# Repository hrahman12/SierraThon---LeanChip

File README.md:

<p align="center"><b>Does the 2D design really become the 3D board? LeanChip proves it with the Lean 4 kernel,</b><br>
for the Sierrathon RP2040 board and its exact 21-line parts list.</p>

# LeanChip: 2D → 3D, verified in Lean

*Built for Sierrathon 2026: design a manufacturable, cost-effective board from the provided RP2040 schematic and BOM.*

## The question

A PCB starts as flat documents: a schematic, a parts list, a stack-up drawing, footprints. It ends as a physical object. **Does the first really turn into the second?**

| 2D design | Lean ⊢ | 3D board |
|---|---|---|
| Schematic pins and nets, BOM part numbers, footprints and courtyards, the 4-layer stack-up | Right part on every footprint, every pin on the right net, every 3D body inside its courtyard, no two parts able to collide, everything on the board | A KiCad STEP assembly with real part models: 49 bodies on a 52 × 45 mm hexagon, 59.5 mil thick |

You feed the tool a board file. It answers 🟢 **green** (proved), 🟡 **yellow** (buildable, needs an action) or 🔴 **red** (not the design you meant). The answer only counts when the Lean kernel has certified it.

## See it run

```
$ python3 leanvsdfm/tools/leancheck.py leanvsdfm/pcb/sierrathon.kicad_pcb

  Board
     GREEN    Every schematic part is placed and on the BOM
     GREEN    Footprint package matches the BOM part number
     YELLOW   Manufacturer footprint used (not a library stand-in)      J1, SW1, SW2, SW3
     GREEN    Every schematic pin is on the right net (schematic ↔ PCB)
     GREEN    No connections that are not on the schematic
     GREEN    LED polarity (cathode to GND)
     GREEN    U3 land pattern = manufacturer (UltraLibrarian)
     GREEN    Preferred land pattern (IPC nominal / manufacturer), not a variant
  3D fit
     GREEN    Every 3D body sits inside its own courtyard
     GREEN    No two courtyards overlap, so no two bodies can collide
     GREEN    Pads and bodies are on the board (inside the outline)
     GREEN    Every drilled hole is at least 8 mil
     YELLOW   Every part has a 3D body model                            J1
  Package
     YELLOW   BOM quantities match the designator lists                 row 5: qty 8 but 7 designators
     YELLOW   Inner copper: stack-up agrees with instructions           0.5 oz vs 1 oz
     GREEN    Stack-up thickness within 62 mil ± 10 %                   59.5 mil
     GREEN    90 Ω pairs use the stack-up geometry (5/4 mil), all other nets ≥ 6 mil
  Specs
     YELLOW   LED current within the RP2040 default 4 mA drive          needs the 8 mA setting
     GREEN    AP2112 junction temperature < 125 °C                      106 °C worst case
     GREEN    USB clock exactly 48 MHz
     GREEN    QSPI clock within W25Q128 limit

  OVERALL  YELLOW    certified by the Lean kernel (decide +kernel)
  3D envelope: board 1.5112 mm + tallest body 4.3 mm = 5.811 mm   | theorem: no two bodies overlap
```

Detail text is shortened here. The same run as an HTML report: [`leanvsdfm/reports/sierrathon.html`](leanvsdfm/reports/sierrathon.html) ([picture](leanvsdfm/reports/sierrathon.png)).

## The 3D board

This is a render of [`leanvsdfm/out3d/sierrathon.step`](leanvsdfm/out3d), the STEP file **KiCad exported from our placed board**, with KiCad's own 3D part models and the manufacturer's model for the flash chip. Nothing in it is drawn by hand.

- **54 parts** placed in a 52 × 45 mm hexagon, zero courtyard overlaps, the four M4 holes included.
- **49 measured bodies.** OpenCascade measures each 3D model; Lean places it from the footprint's position and rotation.
- **Lean and KiCad agree.** KiCad's STEP exporter places the same models on its own. The two agree on all 49 body outlines to under 0.05 µm; heights differ by a fixed 50 µm. That comparison is a test (`tools/check_step_agreement.py`), not a proof.
- **The real stack-up is in the KiCad file:** 59.496 mil, layer by layer, from the Sierrathon drawing.

## How it works

```mermaid
flowchart LR
    A["2D design<br/>schematic · BOM · stack-up · footprints"] --> B["KiCad API reads the board<br/>exact nanometres"]
    M["3D part models<br/>STEP files"] --> C["OpenCascade measures<br/>each body"]
    B --> L{"Lean checks<br/>parts · pins · 3D fit · specs"}
    C --> L
    L -->|"all proved"| G["🟢 GREEN"]
    L -->|"needs an action"| Y["🟡 YELLOW"]
    L -->|"not the intended design"| R["🔴 RED"]
    L --> K["Kernel certifies the findings<br/>as a theorem"]
    R --> F["Fixer searches real options<br/>and proves the fix"]
    F --> B
    style L fill:#1A1F2B,stroke:#B9A7FF,color:#F3EFE6
    style K fill:#1A1F2B,stroke:#B9A7FF,color:#F3EFE6
```

The heart of the 3D check is one theorem, proved once for every possible board ([`Fit3D.lean`](leanvsdfm/LeanVsDFM/Fit3D.lean)):

```lean
/-- If the checker accepts a board, no two part bodies overlap. -/
theorem bodies_never_collide (ps : List Part) (h : fitOk ps = true) : ps.Pairwise bodySep
```

and then applied to our board, where the kernel checks the hypothesis ([`Verify.lean`](leanvsdfm/LeanVsDFM/Verify.lean)):

```lean
theorem our_board_fits : Fit3D.fit3d PcbData.outline PcbData.parts = [] := by decide +kernel

theorem our_board_bodies_never_collide : PcbData.parts.Pairwise Fit3D.bodySep :=
  Fit3D.bodies_never_collide _ (by decide +kernel)
```

`leancheck` does the same for any board you give it: it writes `theorem certified : verify board = [the findings]` and asks the kernel. If the kernel says no, the report says **not certified**.

### Lean and DFM look at different things

| | A DFM check | Lean, here |
|---|---|---|
| Looks at | Fabrication geometry: trace width and spacing, drills, annular rings, solder mask | Intent: the schematic, the BOM, the part numbers, the measured bodies |
| A footprint for the wrong part, with clean geometry | passes | 🔴 wrong package |
| A reversed LED | passes | 🔴 polarity and wrong net |
| The mandated 5/4 mil USB pairs under one global 6 mil rule | flags them | 🟢 knows which nets are impedance nets |
| Result | a list of warnings | a theorem the kernel has checked |

We did not run a commercial DFM tool on this board (it is not routed yet); this table compares what each kind of check examines.

## Demo boards

Five real KiCad files in [`leanvsdfm/pcb/`](leanvsdfm/pcb): our board, and the same board with one realistic mistake each. Every verdict is certified.

| Board | Verdict | What Lean reports |
|---|---|---|
| `sierrathon.kicad_pcb` (ours) | 🟡 YELLOW | Board and 3D fit proved; 4 parts on library stand-ins, J1 has no 3D model, plus the package issues below |
| `fault_led_reversed` | 🔴 RED | D5 pad 1 on `LED3_A`, schematic says `GND`; cathode not on GND |
| `fault_narrow_flash` | 🔴 RED | U3 is `SOIC-8_3.9x4.9mm`; the W25Q128JVSIQ needs `SOIC-8_5.23x5.23mm` |
| `fault_wrong_cap_size` | 🔴 RED | C4 is 0603 on an 0402 line **and** its courtyard now overlaps its neighbours |
| `fault_flash_pins_swapped` | 🔴 RED | U3 pad 2 on `QSPI_D0`, schematic says `QSPI_D1` (and pad 5 the reverse) |

## AI proposes, Lean decides

Anything may propose a way to build the board: a script, or an AI. Proposers are untrusted. Each proposal becomes a real board file with the footprints swapped in place, and Lean rates it. **51 builds, all certified: 16 yellow, 35 red.**

These six were written by Claude, with a reason for each, before Lean rated them ([`explore/ai_proposals.json`](leanvsdfm/explore/ai_proposals.json)):

| AI proposal | Its reasoning | Lean | Why |
|---|---|---|---|
| Keep it nominal | IPC-nominal land patterns everywhere and the manufacturer pattern for the flash: the safest choice for reflow assembly. | 🟡 YELLOW | same as our build |
| Thermal vias under the rp2040 | Use KiCad's thermal-via QFN footprint so the exposed pad can dump heat into the inner planes. | 🔴 RED | the footprint's 0.2 mm vias are below the 8 mil minimum drill |
| Hand-solder the big passives | The 0603 and 0805 parts are the ones a person would rework by hand, so give only those the longer hand-solder pads. | 🟡 YELLOW | fits; reported as variant land patterns |
| Wider soic for the flash | KiCad's 5.275 mm SOIC-8 footprint also targets 208 mil bodies and has slightly longer pads. | 🟡 YELLOW | fits; reported as a variant land pattern |
| Hand-solder the crystal | The 3225 crystal has pads under the body; the hand-solder footprint exposes them for an iron. | 🔴 RED | its larger courtyard overlaps R7, R13, R14 and R17 |
| Hand-solder leds and regulator | LEDs are polarised and often replaced, and the regulator is the hottest part; longer pads make both easier to rework. | 🟡 YELLOW | fits; reported as variant land patterns |

Two plausible ideas were wrong, and Lean said exactly why.

Changing **one** BOM line to its hand-solder variant stays yellow for most lines, but turns red for the 27 Ω USB resistors, the ESD chip and the crystal, because their larger courtyards collide on this compact board.

## Where the supplied package breaks

Four problems in the official Sierrathon files, marked on the files themselves. Each is a Lean theorem in [`Breaks.lean`](leanvsdfm/LeanVsDFM/Breaks.lean).

| # | Break | Lean catches it | Fix |
|---|---|---|---|
| 1 | BOM row 5 says **Qty 8**, lists **7** designators; the schematic draws 7 LEDs | `break1_only_row5`, `break1_schematic_has_7_leds` | set quantity to the designator count; only row 5 changes (`break1_fix_changes_only_row5`) |
| 2 | Stack-up draws **0.5 oz** inner copper; instructions say **1 oz** | `break2_conflict` | ask the fab; both readings meet 62 mil ± 10 % (`break2_both_readings_buildable`) |
| 3 | 330 Ω LEDs draw up to **4.945 mA**, above the RP2040's 4 mA default pin drive | `break3_default_drive_fails` | set GPIO17–23 to 8 mA (`break3_fixed_by_8mA`); BOM unchanged |
| 4 | The mandated **5/4 mil** 90 Ω pairs fail a global **6 mil** rule | `break4_dfm_flags_mandated_geometry` | rule per net class (`break4_lean_accepts_pairs`, `break4_lean_still_enforces_6mil`) |

## The proofs, as formulas

Each formula is a theorem the Lean kernel has checked.

**No two bodies overlap** (`Fit3D.bodies_never_collide`, with `Fit3D.sep_of_inside`):

$$\text{fitOk}(ps)\ \Longrightarrow\ \forall\, p \neq q:\ \text{body}(p)\cap\text{body}(q)=\varnothing \qquad\qquad a\subseteq A,\ b\subseteq B,\ A\cap B=\varnothing\ \Longrightarrow\ a\cap b=\varnothing$$

**Where a 3D body lands on the board** (`Fit3D.bodyBox`), with θ a right angle:

$$\binom{x}{y}_{\text{board}}=\binom{p_x}{p_y}+R_\theta\binom{m_x}{-m_y}$$

**Inside the convex board outline** (`Fit3D.pointIn`): the cross product has one sign for every edge (a, b):

$$(b-a)\times(c-a)\ \ge 0$$

**Stack-up thickness** (`Specs.stackup_within_tolerance`):

$$0.5+1.5+4.348+0.6+45.6+0.6+4.348+1.5+0.5 = 59.496\ \text{mil} \in 62 \pm 10\%$$

**LED current** (`Breaks.break3_default_drive_fails`, `Fixers.led_design`):

$$I_{\max}=\frac{V_{DD,\max}-V_{f,\min}}{0.95\,R}=\frac{3.35-1.8}{313.5\ \Omega}=4.945\ \text{mA} > 4\ \text{mA}, \qquad 7\,I_{\max} = 34.6\ \text{mA} \le 50\ \text{mA}$$

**Regulator junction temperature** (`Specs.ldo_junction_ok`):

$$T_j = T_a + \theta_{JA}\,(V_{BUS,\max}-V_{out,\min})\,I = 50 + 250\cdot 2.0\cdot 0.112 = 106^\circ\text{C} < 125^\circ\text{C}$$

**Crystal load** (`Specs.crystal_load_window`), for every stray capacitance from 2 to 5 pF:

$$C_L=\frac{C_6C_7}{C_6+C_7}+C_s = 7.5 + C_s \in [9.5,\ 12.5]\ \text{pF}$$

**ADC supply filter** (`Specs.adc_filter_corner`), for every in-tolerance R and C and every π between 3.141 and 3.142:

$$313 \le \frac{1}{2\pi RC} \le 424\ \text{Hz}$$

**Differential impedance in tolerance** (`Breaks.break4_impedance_in_tolerance`), **BOM self-consistency** (`Breaks.break1_only_row5`), **fixers are correct** (`Fixers.find?_sound`), **overall colour is the worst row** (`Report.overall_is_worst`):

$$0.9\cdot 90 \le 89.7 \le 1.1\cdot 90\ \Omega \qquad \lbrace r : \text{qty}(r)\ne \text{count}(r)\rbrace=\lbrace 5\rbrace \qquad \text{find?}\ p\ l=\text{some}\ a \Rightarrow p(a)\wedge a\in l \qquad \forall r:\ \text{rank}(r)\le\text{rank}(\text{overall})$$

The [theorem table](docs/THEOREMS.md) covers 98 theorems across seven modules, including the web checker. The proofs use Lean's three standard axioms.

## Figures

| | |
|---|---|
|  |  |
|  |  |
|  |  |
|  |  |

Every figure is drawn from real data: the certified runs, the KiCad board, or the exact functions proved in Lean (`leanvsdfm/tools/viz.py`).

## With Claude Code

The repository ships slash commands and a skill ([`.claude/`](.claude)), so you can ask in plain words.

| Command | What it does |
|---|---|
| `/leancheck [board]` | Verdict for a board, row by row |
| `/explore [n]` | Propose n builds and let Lean rate them |
| `/verify` | Rebuild every proof and audit the axioms |
| `/board3d` | Export STEP and test it against Lean's placement |

A real exchange from building this project:

```
You:    Does Lean's idea of where the parts are in 3D match KiCad's STEP export?
Claude: $ python3 tools/check_step_agreement.py out3d/sierrathon_parts.json
        49 Lean bodies vs 49 bodies in KiCad's STEP export: largest outline (x, y)
        difference 0.0 µm, largest height difference 50 µm -> PASS
```

## Run it locally

You need Lean 4 (through elan) and KiCad 7 with its Python module. On Windows, use WSL with Ubuntu 24.04.

```bash
sudo apt install kicad kicad-footprints
```

```bash
curl -sSf https://raw.githubusercontent.com/leanprover/elan/master/elan-init.sh | sh
```

```bash
cd leanvsdfm && lake build
```

```bash
python3 tools/leancheck.py pcb/sierrathon.kicad_pcb --html report.html
```

`lake build` checks every proof. In text and JSON modes, `leancheck` exits 0 for certified green or yellow, 3 for red, and 4 if certification fails. The web API returns a red report with HTTP 422. Yellow findings are accepted design warnings and still require review.

From the repository root, run the fabrication gate separately with KiCad 9.

```bash
python3 leanvsdfm/tools/check_drc.py leanvsdfm/pcb/sierrathon.kicad_pcb --report /tmp/sierrathon-drc.json
```

This command exits 3 for DRC errors or unconnected items, 0 when only warnings or no findings remain, and 2 if DRC cannot run.

Check the exported component solids with OpenCascade using the `OCP` Python module.

```bash
python3 leanvsdfm/tools/check_step_collisions.py leanvsdfm/out3d/sierrathon.step --expected-components 49
```

The check uses OpenCascade solid intersections for candidate pairs. Shared volume above `1e-9 mm³` blocks the check. The expected count covers the modeled components in the current export and excludes the PCB substrate.

For live proposals on Vercel, set `ANTHROPIC_API_KEY` as a sensitive server-side variable for the project's Production environment, then redeploy. If the Anthropic project requires a different model, set `LEANCHIP_MODEL` to a model ID available to that project.

## Repository

```
├── leanvsdfm/               the project
│   ├── LeanVsDFM/           Lean: PartsVerifier · Fit3D · Breaks · Fixers · Specs · Report · Verify
│   ├── tools/               leancheck, board builder and placer, STEP tools, explorer, figures
│   ├── pcb/                 our board and four fault boards (KiCad 7)
│   ├── out3d/               the STEP and GLB that KiCad and OpenCascade produced
│   ├── models3d/            the 3D part models used, with their measured sizes
│   ├── explore/             51 rated builds, including the AI proposals
│   └── reports/             HTML reports
├── netlist/                 the schematic as a netlist (transcribed from the PDF)
├── altium/                  Altium symbol and footprint libraries
├── site/                    the website
├── assets/                  banner, figures, the marked-up Sierrathon files
├── .claude/                 Claude Code commands and skill
└── archive/                 earlier directions, kept for history
```

## What this does not do yet

- **Fabrication is blocked.** KiCad 9.0.2 DRC reports 124 unconnected items and 79 silkscreen warnings on the supplied board. Routing and a fabrication-ready DFM review remain open.
- **Four parts use library stand-ins** (USB-C J1, switches SW1 to SW3). Their manufacturer footprints and 3D models are needed; the report keeps them yellow until then.
- **3D fit has two checks.** Lean proves separation for the measured bounding boxes. OpenCascade checks shared solid volume directly in the STEP export. The current export covers 49 component bodies and is missing J1.
- **Schematic provenance.** `python3 netlist/build_netlist.py --check` verifies the supplied PDF and BOM hashes and reproduces the 39-net transcription. Comparing connectivity directly with the schematic requires the native EDA design or its exported netlist.
- **Electrical inputs.** Raspberry Pi's SDK confirms the 4 mA reset setting and the nominal 2, 4, 8 and 12 mA pad-drive options. The thermal resistance, ambient temperature, load budget, LED forward voltage and stray capacitance still need design-specific validation. [RP2040 pad registers](https://github.com/raspberrypi/pico-sdk/blob/2.2.0/src/rp2040/hardware_regs/include/hardware/regs/pads_bank0.h)

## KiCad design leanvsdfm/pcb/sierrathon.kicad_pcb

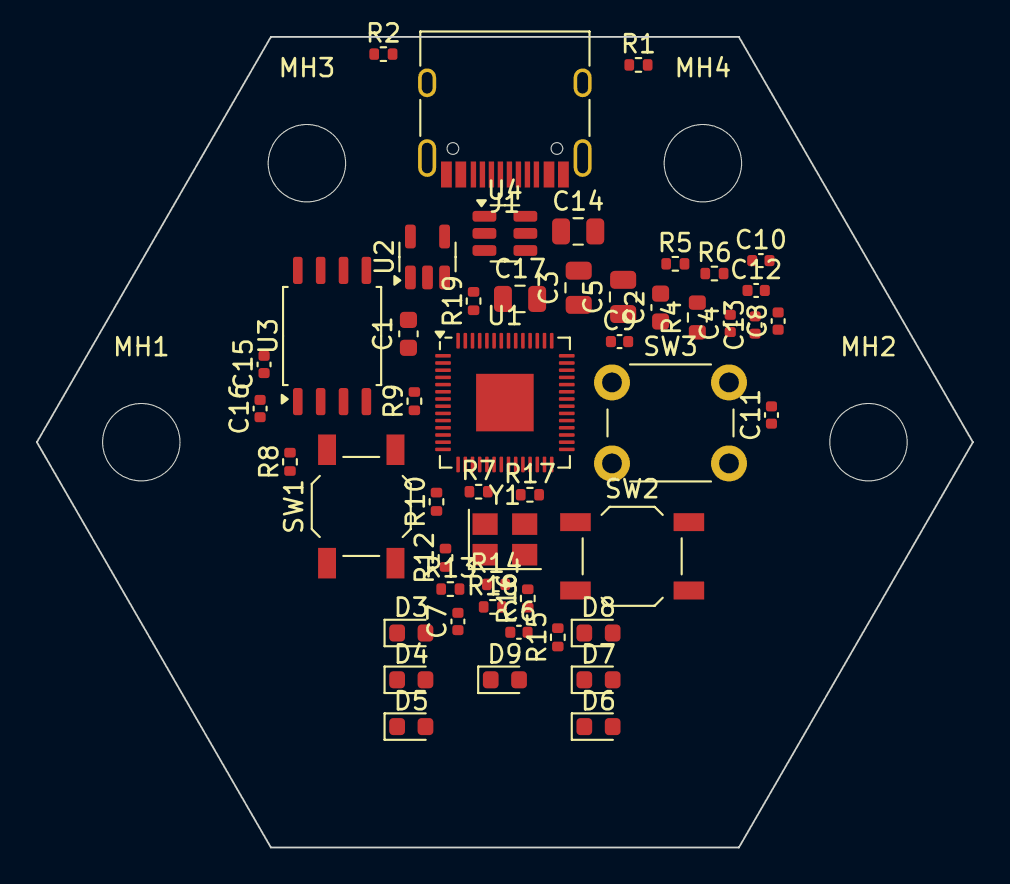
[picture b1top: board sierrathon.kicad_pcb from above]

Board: 4 copper layers, 52.0 x 45.0 mm, 54 parts (0 on the bottom side), 39 nets, no tracks yet.

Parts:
C1, C2: 1uF; C_0603_1608Metric
C3, C5, C14, C17: 2.2uF; C_0805_2012Metric
C4, C8, C9, C10, C11, C12, C13, C15, C16: 0.1uF; C_0402_1005Metric
C6, C7: 15pF; C_0402_1005Metric
D3, D4, D5, D6, D7, D8, D9: LED; LED_0603_1608Metric
J1: USB-C; USB_C_Receptacle_HRO_TYPE-C-31-M-12
MH1, MH2, MH3, MH4: Mounting Hole; MountingHole_4.3mm_M4
R1, R2: 5.1K; R_0402_1005Metric
R4: 200; R_0603_1608Metric
R5, R6: 27; R_0402_1005Metric
R7, R8: 1K; R_0402_1005Metric
R9, R10, R19: 10K; R_0402_1005Metric
R12, R13, R14, R15, R16, R17, R18: 330; R_0402_1005Metric
SW1: BOOT; SW_SPST_TL3342
SW2: RESET; SW_SPST_TL3342
SW3: SWITCH; SW_PUSH_6mm
U1: RP2040; QFN-56-1EP_7x7mm_P0.4mm_EP3.2x3.2mm
U2: AP2112; SOT-23-5
U3: W25Q128JVSIQ; SOIC-8_5.23x5.23mm_P1.27mm
U4: USBLC6-2SC6; SOT-23-6
Y1: CRYSTAL14; Crystal_SMD_3225-4Pin_3.2x2.5mm

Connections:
+1.1V: C15.1, C16.1, C17.1, U1.23, U1.45, U1.50
+3.3V: C2.1, C3.1, C4.1, C8.1, C9.1, C10.1, C11.1, C12.1, C13.1, C14.1, R4.1, R9.1, R10.1, R19.1, U1.1, U1.10, U1.22, U1.33, U1.42, U1.44, U1.48, U1.49, U2.5, U3.8
ADC_AVDD: C5.1, R4.2, U1.43
BOOT: R8.1, SW1.1
CC1: J1.A5, R1.1
CC2: J1.B5, R2.1
D_N: J1.A7, J1.B7, U4.3
D_P: J1.A6, J1.B6, U4.1
GND: C1.2, C2.2, C3.2, C4.2, C5.2, C6.1, C7.1, C8.2, C9.2, C10.2, C11.2, C12.2, C13.2, C14.2, C15.2, C16.2, C17.2, D3.1, D4.1, D5.1, D6.1, D7.1, D8.1, D9.1, J1.A1, J1.A12, J1.B1, J1.B12, J1.S1, R1.2, R2.2, SW1.2, SW2.2, SW3.2, U1.19, U1.57, U2.2, U3.4, U4.2, Y1.2, Y1.4
LED1_A: D3.2, R12.2
LED2_A: D4.2, R13.2
LED3_A: D5.2, R14.2
LED4_A: D6.2, R15.2
LED5_A: D7.2, R16.2
LED6_A: D8.2, R17.2
LED7_A: D9.2, R18.2
Led1: R12.1, U1.28
Led2: R13.1, U1.29
Led3: R14.1, U1.30
Led4: R15.1, U1.31
Led5: R16.1, U1.32
Led6: R17.1, U1.34
Led7: R18.1, U1.35
QSPI_CLK: U1.52, U3.6
QSPI_CS: R8.2, R9.2, U1.56, U3.1
QSPI_D0: U1.53, U3.5
QSPI_D1: U1.55, U3.2
QSPI_D2: U1.54, U3.3
QSPI_D3: U1.51, U3.7
RESET: R10.2, SW2.1, U1.26
SW: R19.2, SW3.1, U1.36
USBR_N: R5.2, U1.46
USBR_P: R6.2, U1.47
USB_N: R5.1, U4.4
USB_P: R6.1, U4.6
VBUS: C1.1, J1.A4, J1.A9, J1.B4, J1.B9, U2.1, U2.3, U4.5
XIN: C6.2, U1.20, Y1.1
XOUT: R7.2, U1.21
XOUT_XTAL: C7.2, R7.1, Y1.3

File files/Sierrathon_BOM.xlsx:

SL.NO | REFDES | QTY | Value | Manufacturer Part Number | Manufacturer | Description | DNI
1 | C1,C2 | 2 | 1uF | GCM188R71C105KA64D | Murata Electronics | CAP CER 1UF 16V X7R 0603
2 | C3,C5,C14,C17 | 4 | 2.2uF | GCM21BR71C225KA64L | Murata Electronics | CAP CER 2.2UF 16V X7R 0805
3 | C4,C8,C9,C10,C11,C12,C13,C15,C16 | 9 | 0.1uF | GCM155R71C104KA55D | Murata Electronics | CAP CER 0.1UF 16V X7R 0402
4 | C6,C7 | 2 | 15pF | GCM1555C1H150JA16D | Murata Electronics | CAP CER 15PF 50V C0G/NP0 0402
5 | D3,D4,D5,D6,D7,D8,D9 | 8 | LED | QBLP601-R5 | QT Brightek (QTB) | LED RED CLEAR 625NM 0603 SMD
6 | J1 | 1 | USB-C | UJ20-C-H-G-SMT-TR | Same Sky (Formerly CUI Devices) | CONN RCPT USB 2.0 TYPE C PCB RA
7 | MH1,MH2,MH3,MH4 | 4 | Mounting Hole |  |  |  | DNI
8 | R1,R2 | 2 | 5.1K | RC0402JR-075K1L | YAGEO | RES 5.1K OHM 5% 1/16W 0402
9 | R4 | 1 | 200 | RC0603JR-07200RL | YAGEO | RES 200 OHM 5% 1/10W 0603
10 | R5,R6 | 2 | 27 | RC0402FR-0727RL | YAGEO | RES 27 OHM 1% 1/16W 0402
11 | R7,R8 | 2 | 1K | RC0402FR-071KL | YAGEO | RES 1K OHM 1% 1/16W 0402
12 | R9,R10,R19 | 3 | 10K | RC0402JR-0710KL | YAGEO | RES 10K OHM 5% 1/16W 0402
13 | R12,R13,R14,R15,R16,R17,R18 | 7 | 330 | AF0402JR-07330RL | YAGEO | RES SMD 330 OHM 5% 1/16W 0402
14 | SW1 | 1 | BOOT | PTS526SM15SMTR2 LFS | C&K | SWITCH TACTILE SPST-NO 0.05A 12V
15 | SW2 | 1 | RESET | PTS526SM15SMTR2 LFS | C&K | SWITCH TACTILE SPST-NO 0.05A 12V
16 | SW3 | 1 | SWITCH | D6R90 F2 LFS | C&K | SWITCH PUSH SPST-NO 0.1A 32V
17 | U1 | 1 | RP2040 | SC0914(13) | Raspberry Pi | IC MCU 32BIT EXT MEM 56QFN
18 | U2 | 1 | AP2112 | AP2112K-3.3TRG1 | Diodes Incorporated | IC REG LINEAR 3.3V 600MA SOT-25
19 | U3 | 1 | W25Q128JVSIQ | W25Q128JVSIQ TR | Winbond Electronics | IC FLASH 128MBIT SPI/QUAD 8SOIC
20 | U4 | 1 | USBLC6-2SC6 | USBLC6-2SC6 | STMicroelectronics | TVS DIODE 5.25VWM 17VC SOT23-6
21 | Y1 | 1 | CRYSTAL14 | ABM8-272-T3 | Abracon LLC | CRYSTAL 12.0000MHZ 10PF SMD
